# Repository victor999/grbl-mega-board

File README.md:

# grbl-mega-board
Board for grbl-mega 5 axis project

https://github.com/fra589/grbl-Mega-5X

Designed in Eagle

Connectors designed with approach to direct connection to drivers without swapping wires - first pin on connector, first pin on driver and so on

Tested in XYZXAB CNC configuration with MIN limit switches and TB6600 drivers. 

It means double X axis with separate limit switches, so no problems with squaring

Can be configured also for double Y or whatever you want

Current config is for XYZX

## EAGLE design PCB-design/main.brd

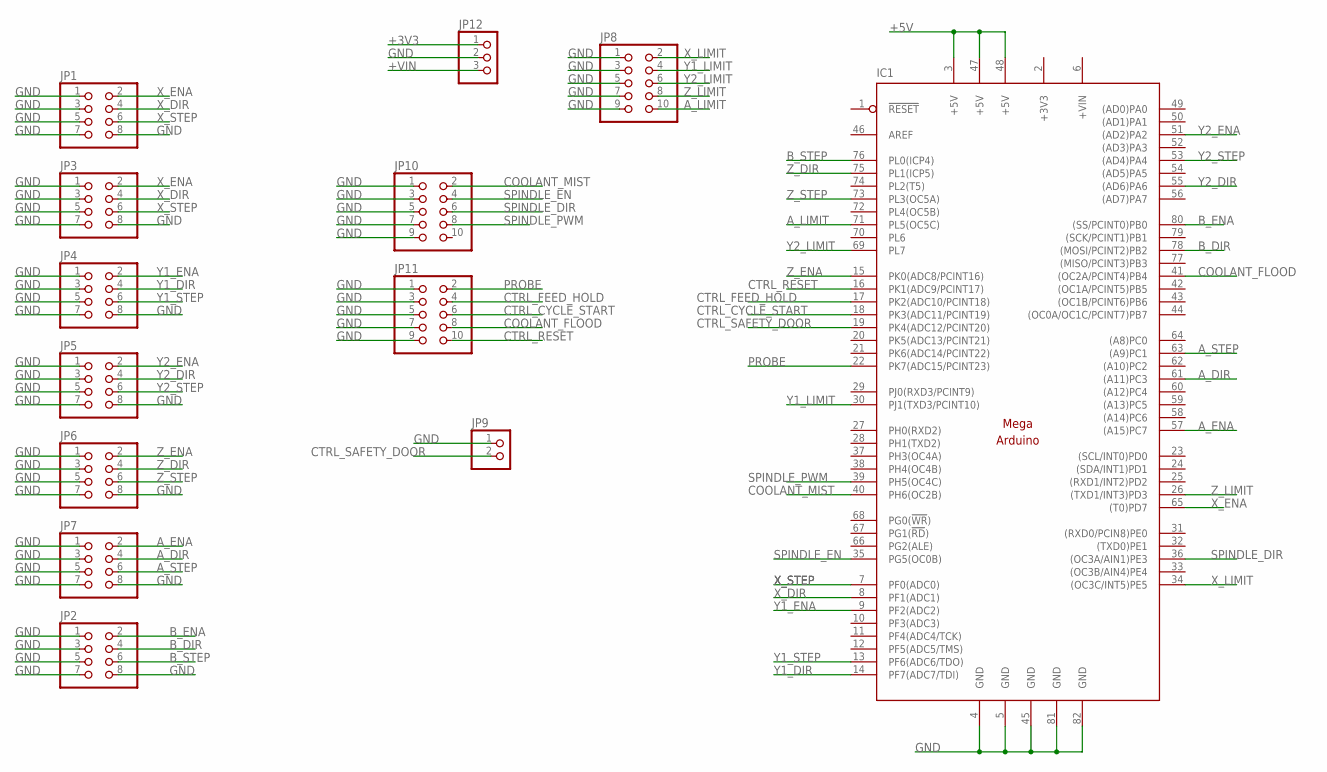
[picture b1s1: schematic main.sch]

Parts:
IC1: MEGAARDUINO_1; MEGA_ARDUINO
JP1, JP2, JP3, JP4, JP5, JP6, JP7: PINHD-2X4; 2X04
JP8, JP10, JP11: PINHD-2X5; 2X05
JP9: PINHD-1X2; 1X02
JP12: PINHD-1X3; 1X03

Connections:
+3V3: IC1.2 (+3V3), JP12.1
+5V: IC1.3 (+5V), IC1.47 (+5V), IC1.48 (+5V)
+VIN: IC1.6 (+VIN), JP12.3
A_DIR: IC1.61 ((A11)PC3), JP7.4
A_ENA: IC1.57 ((A15)PC7), JP7.2
A_LIMIT: IC1.71 (PL5(OC5C)), JP8.10
A_STEP: IC1.63 ((A9)PC1), JP7.6
B_DIR: IC1.78 ((MOSI/PCINT2)PB2), JP2.4
B_ENA: IC1.80 ((SS/PCINT0)PB0), JP2.2
B_STEP: IC1.76 (PL0(ICP4)), JP2.6
COOLANT_FLOOD: IC1.41 ((OC2A/PCINT4)PB4), JP11.8
COOLANT_MIST: IC1.40 (PH6(OC2B)), JP10.2
CTRL_CYCLE_START: IC1.18 (PK3(ADC11/PCINT19)), JP11.6
CTRL_FEED_HOLD: IC1.17 (PK2(ADC10/PCINT18)), JP11.4
CTRL_RESET: IC1.16 (PK1(ADC9/PCINT17)), JP11.10
CTRL_SAFETY_DOOR: IC1.19 (PK4(ADC12/PCINT20)), JP9.2
GND: IC1.4 (GND), IC1.5 (GND), IC1.45 (GND), IC1.81 (GND), IC1.82 (GND), JP1.1, JP1.3, JP1.5, JP1.7, JP1.8, JP2.1, JP2.3, JP2.5, JP2.7, JP2.8, JP3.1, JP3.3, JP3.5, JP3.7, JP3.8, JP4.1, JP4.3, JP4.5, JP4.7, JP4.8, JP5.1, JP5.3, JP5.5, JP5.7, JP5.8, JP6.1, JP6.3, JP6.5, JP6.7, JP6.8, JP7.1, JP7.3, JP7.5, JP7.7, JP7.8, JP8.1, JP8.3, JP8.5, JP8.7, JP8.9, JP9.1, JP10.1, JP10.3, JP10.5, JP10.7, JP10.9, JP11.1, JP11.3, JP11.5, JP11.7, JP11.9, JP12.2
PROBE: IC1.22 (PK7(ADC15/PCINT23)), JP11.2
SPINDLE_DIR: IC1.36 ((OC3A/AIN1)PE3), JP10.6
SPINDLE_EN: IC1.35 (PG5(OC0B)), JP10.4
SPINDLE_PWM: IC1.39 (PH5(OC4C)), JP10.8
X_DIR: IC1.8 (PF1(ADC1)), JP1.4, JP3.4
X_ENA: IC1.65 ((T0)PD7), JP1.2, JP3.2
X_LIMIT: IC1.34 ((OC3C/INT5)PE5), JP8.2
X_STEP: IC1.7 (PF0(ADC0)), JP1.6, JP3.6
Y1_DIR: IC1.14 (PF7(ADC7/TDI)), JP4.4
Y1_ENA: IC1.9 (PF2(ADC2)), JP4.2
Y1_LIMIT: IC1.30 (PJ1(TXD3/PCINT10)), JP8.4
Y1_STEP: IC1.13 (PF6(ADC6/TDO)), JP4.6
Y2_DIR: IC1.55 ((AD6)PA6), JP5.4
Y2_ENA: IC1.51 ((AD2)PA2), JP5.2
Y2_LIMIT: IC1.69 (PL7), JP8.6
Y2_STEP: IC1.53 ((AD4)PA4), JP5.6
Z_DIR: IC1.75 (PL1(ICP5)), JP6.4
Z_ENA: IC1.15 (PK0(ADC8/PCINT16)), JP6.2
Z_LIMIT: IC1.26 ((TXD1/INT3)PD3), JP8.8
Z_STEP: IC1.73 (PL3(OC5A)), JP6.6

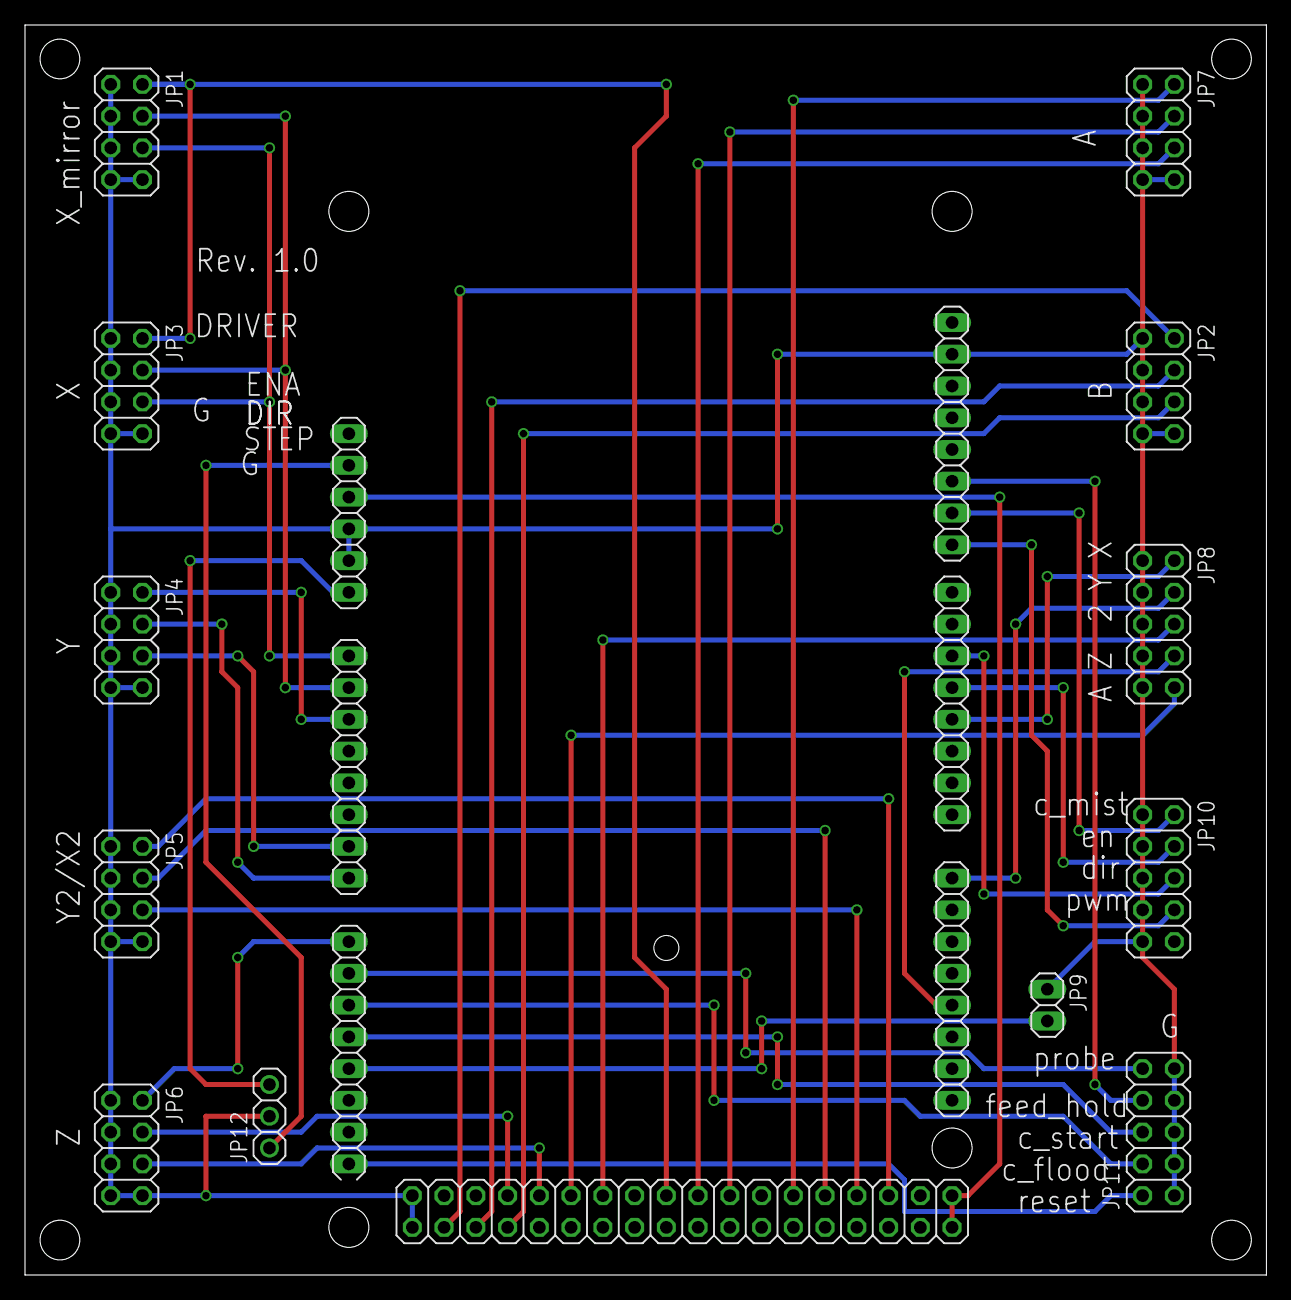
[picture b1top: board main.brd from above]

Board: 2 copper layers, 99.3 x 100.0 mm, 13 parts (0 on the bottom side), 37 nets.

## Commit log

2021-01-29 Firsdt release
2021-01-29 Update photos and Readme
